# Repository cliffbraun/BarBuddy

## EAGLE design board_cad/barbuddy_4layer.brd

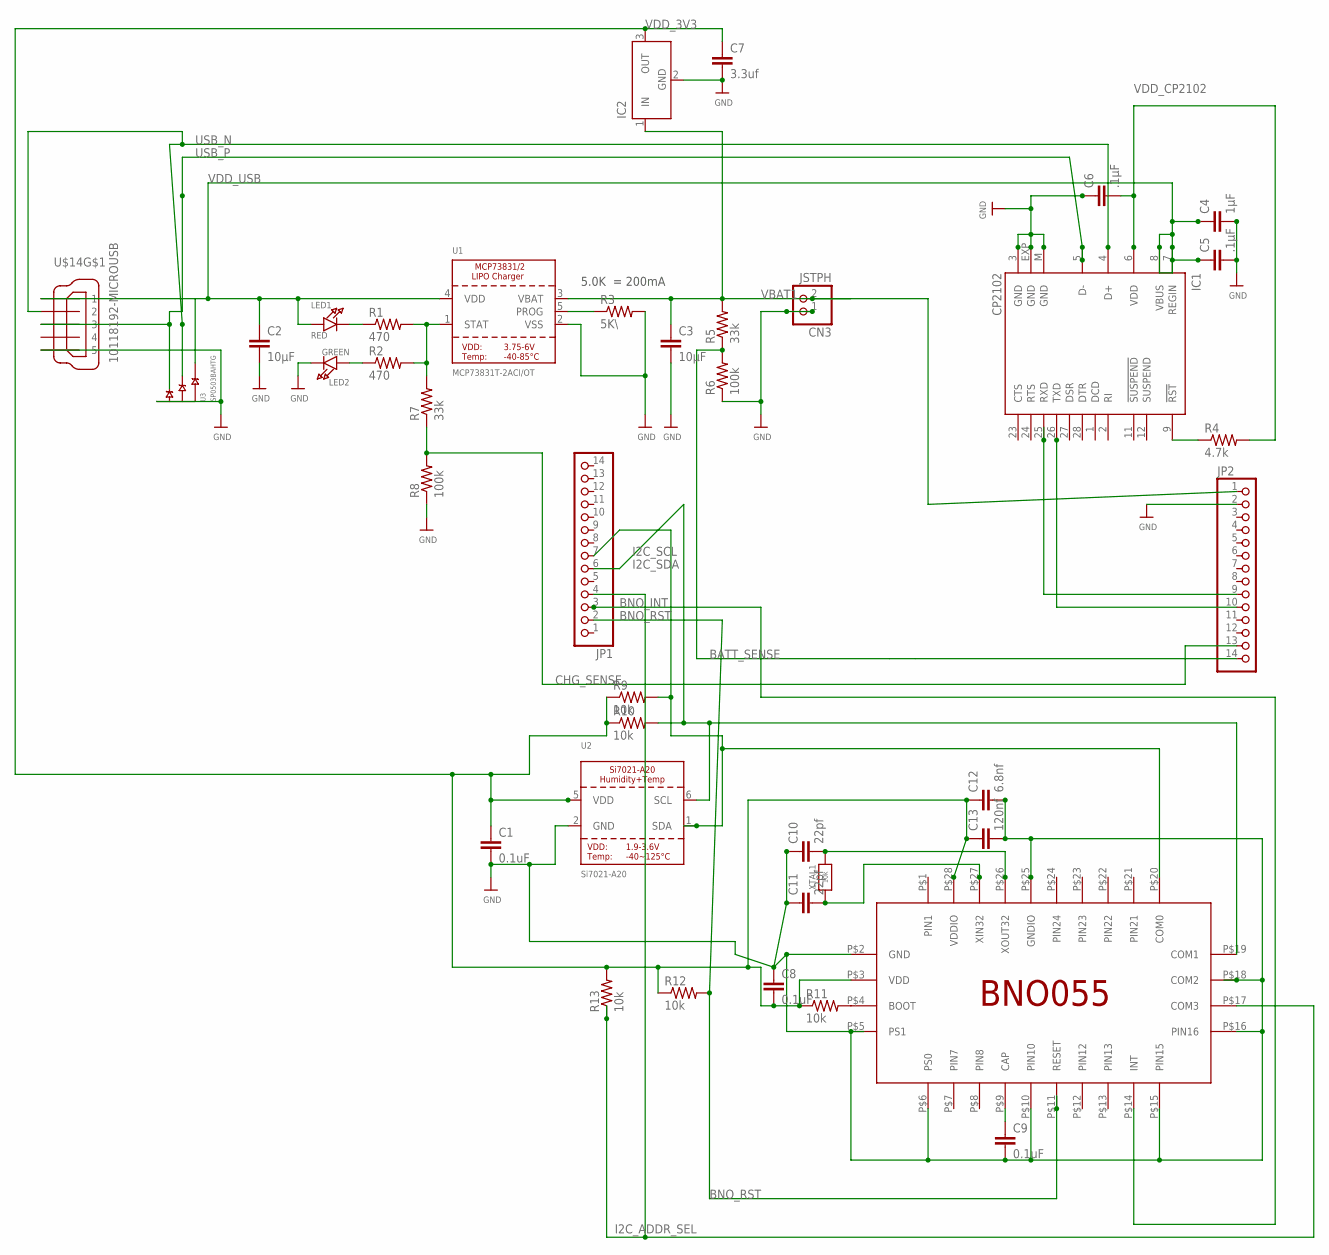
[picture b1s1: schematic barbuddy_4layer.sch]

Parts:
BNO055: BNO055; LGA-28
C1, C8, C9: 0.1uF; C0402
C2, C3: 10µF; C0402
C4: 1µF; C0402
C5, C6: .1µF; C0402
C7: 3.3uf; C0402
C10, C11: 22pf; C0402
C12: 6.8nf; C0402
C13: 120nf; C0402
CN3: JSTPH; JSTPH2
IC1: CP2102; MLP28
IC2: LT1129CST5; SOT223
JP1, JP2: PINHD-1X14; 1X14
LED1: RED; CHIPLED_0805_NOOUTLINE
LED2: GREEN; CHIPLED_0805_NOOUTLINE
R1, R2: 470; R0402
R3: 5K\; R0402
R4: 4.7k; R0402
R5, R7: 33k; R0402
R6, R8: 100k; R0402
R9, R10, R11, R12, R13: 10k; R0402
U1: MCP73831T-2ACI/OT; SOT23-5
U2: Si7021-A20; DFN6_3X3_SI
U3: SP0503BAHTG; SOT143
U$14: 10118192-MICROUSB; MICROUSB-SMT
XTAL1: 10k; 0805-NO

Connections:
BATT_SENSE: JP2.14, R5.1, R6.2
BNO_CAP: BNO055.P$9 (CAP), C9.1
BNO_INT: BNO055.P$14 (INT), JP1.3
BNO_RST: BNO055.P$11 (RESET), JP1.2, R12.2
CHG_PROG: R3.1, U1.5 (PROG)
CHG_SENSE: JP2.13, R7.1, R8.2
CHG_STATUS: R1.2, R2.2, R7.2, U1.1 (STAT)
CP2102_RST: IC1.9 (!RST), R4.1
GND: BNO055.P$2 (GND), BNO055.P$5 (PS1), BNO055.P$6 (PS0), BNO055.P$10 (PIN10), BNO055.P$15 (PIN15), BNO055.P$16 (PIN16), BNO055.P$18 (COM2), BNO055.P$25 (GNDIO), C1.2, C2.2, C3.2, C4.2, C5.2, C6.1, C7.2, C8.1, C9.2, C10.1, C11.1, C12.2, C13.2, CN3.1, IC1.3 (GND), IC1.EXP (GND), IC1.M (GND), IC2.2 (GND), IC2.4 (GND), JP2.2, LED2.C, R3.2, R6.1, R8.1, U1.2 (VSS), U2.2 (GND), U3.1 (GND), U$14.P$5 (5)
I2C_ADDR_SEL: BNO055.P$17 (COM3), JP1.4, R13.1
I2C_SCL: BNO055.P$19 (COM1), JP1.6, R10.2, U2.6 (SCL)
I2C_SDA: BNO055.P$20 (COM0), JP1.7, R9.2, U2.1 (SDA)
unnamed: LED1.C, R1.1
unnamed: BNO055.P$4 (BOOT), R11.2
unnamed: LED2.A, R2.1
UART0_RX: IC1.26 (TXD), JP2.10
UART0_TX: IC1.25 (RXD), JP2.9
USB_N: IC1.4 (D+), U3.3 (B), U$14.P$2 (2)
USB_P: IC1.5 (D-), U3.2 (A), U$14.P$3 (3)
VBAT1: C3.1, CN3.2, IC2.1 (IN), JP2.1, R5.2, U1.3 (VBAT)
VDD_3V3: BNO055.P$3 (VDD), BNO055.P$28 (VDDIO), C1.1, C7.1, C8.2, C12.1, C13.1, IC2.3 (OUT), R9.1, R10.1, R11.1, R12.1, R13.2, U2.5 (VDD)
VDD_CP2102: C6.2, IC1.6 (VDD), R4.2
VDD_USB: C2.1, C4.1, C5.1, IC1.7 (REGIN), IC1.8 (VBUS), LED1.A, U1.4 (VDD), U3.4 (C), U$14.P$1 (1)
X_IN: BNO055.P$27 (XIN32), C11.2, XTAL1.1
X_OUT: BNO055.P$26 (XOUT32), C10.2, XTAL1.2

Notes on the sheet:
5.0K = 200mA

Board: 4 copper layers, 39 parts (16 on the bottom side), 25 nets, no tracks yet.

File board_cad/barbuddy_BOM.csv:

"Part";"Value";"Device";"Package";"Description";"MF";"MPN";"OC_FARNELL";"OC_NEWARK";
"BNO055";"BNO055";"BNO055";"LGA-28";"";"";"";"";"";
"C1";"0.1uF";"C-EUC0402";"C0402";"CAPACITOR, European symbol";"";"";"";"";
"C2";"10µF";"C-EUC0402";"C0402";"CAPACITOR, European symbol";"";"";"";"";
"C3";"10µF";"C-EUC0402";"C0402";"CAPACITOR, European symbol";"";"";"";"";
"C4";"1µF";"C-EUC0402";"C0402";"CAPACITOR, European symbol";"";"";"";"";
"C5";".1µF";"C-EUC0402";"C0402";"CAPACITOR, European symbol";"";"";"";"";
"C6";".1µF";"C-EUC0402";"C0402";"CAPACITOR, European symbol";"";"";"";"";
"C7";"3.3uf";"C-EUC0402";"C0402";"CAPACITOR, European symbol";"";"";"";"";
"C8";"0.1uF";"C-EUC0402";"C0402";"CAPACITOR, European symbol";"";"";"";"";
"C9";"0.1uF";"C-EUC0402";"C0402";"CAPACITOR, European symbol";"";"";"";"";
"C10";"22pf";"C-EUC0402";"C0402";"CAPACITOR, European symbol";"";"";"";"";
"C11";"22pf";"C-EUC0402";"C0402";"CAPACITOR, European symbol";"";"";"";"";
"C12";"6.8nf";"C-EUC0402";"C0402";"CAPACITOR, European symbol";"";"";"";"";
"C13";"120nf";"C-EUC0402";"C0402";"CAPACITOR, European symbol";"";"";"";"";
"CN3";"JSTPH";"JST_2PIN";"JSTPH2";"JST 2-Pin Right-Angle Connector";"";"";"";"";
"IC1";"CP2102";"CP2102";"MLP28";"Single-Chip USB to UART Bridge";"FARNELL";"CP2102-GM";"9282130";"30K5635";
"IC2";"";"LT1129CST5";"SOT223";"VOLTAGE REGULATOR";"";"";"";"";
"JP1";"";"PINHD-1X14";"1X14";"PIN HEADER";"";"";"";"";
"JP2";"";"PINHD-1X14";"1X14";"PIN HEADER";"";"";"";"";
"LED1";"RED";"LED0805_NOOUTLINE";"CHIPLED_0805_NOOUTLINE";"LED";"";"";"";"";
"LED2";"GREEN";"LED0805_NOOUTLINE";"CHIPLED_0805_NOOUTLINE";"LED";"";"";"";"";
"R1";"470";"R-US_R0402";"R0402";"RESISTOR, American symbol";"";"";"";"";
"R2";"470";"R-US_R0402";"R0402";"RESISTOR, American symbol";"";"";"";"";
"R3";"5K\";"R-US_R0402";"R0402";"RESISTOR, American symbol";"";"";"";"";
"R4";"4.7k";"R-US_R0402";"R0402";"RESISTOR, American symbol";"";"";"";"";
"R5";"33k";"R-US_R0402";"R0402";"RESISTOR, American symbol";"";"";"";"";
"R6";"100k";"R-US_R0402";"R0402";"RESISTOR, American symbol";"";"";"";"";
"R7";"33k";"R-US_R0402";"R0402";"RESISTOR, American symbol";"";"";"";"";
"R8";"100k";"R-US_R0402";"R0402";"RESISTOR, American symbol";"";"";"";"";
"R9";"10k";"R-US_R0402";"R0402";"RESISTOR, American symbol";"";"";"";"";
"R10";"10k";"R-US_R0402";"R0402";"RESISTOR, American symbol";"";"";"";"";
"R11";"10k";"R-US_R0402";"R0402";"RESISTOR, American symbol";"";"";"";"";
"R12";"10k";"R-US_R0402";"R0402";"RESISTOR, American symbol";"";"";"";"";
"R13";"10k";"R-US_R0402";"R0402";"RESISTOR, American symbol";"";"";"";"";
"U$13";"";"USB-AB""";"USB-AB-MICRO-SMD_V02_BOSS";"This is a USB AB connector that is compatible with USB OTG. i.e. this connector can serve as a host or device";"";"";"";"";
"U1";"MCP73831T-2ACI/OT";"MCP73831/2";"SOT23-5";"MCP73831/2 LIPO Charger";"";"";"";"";
"U2";"Si7021-A20";"SI7021-A20";"DFN6_3X3_SI";"Si7021-A20 - I2C Humidity and Temperature Sensor";"";"";"";"";
"U3";"SP0503BAHTG";"SP0503BAHTG";"SOT143";"";"";"";"";"";
"XTAL1";"10k";"RESISTOR0805_NOOUTLINE";"0805-NO";"Resistors";"";"";"";"";

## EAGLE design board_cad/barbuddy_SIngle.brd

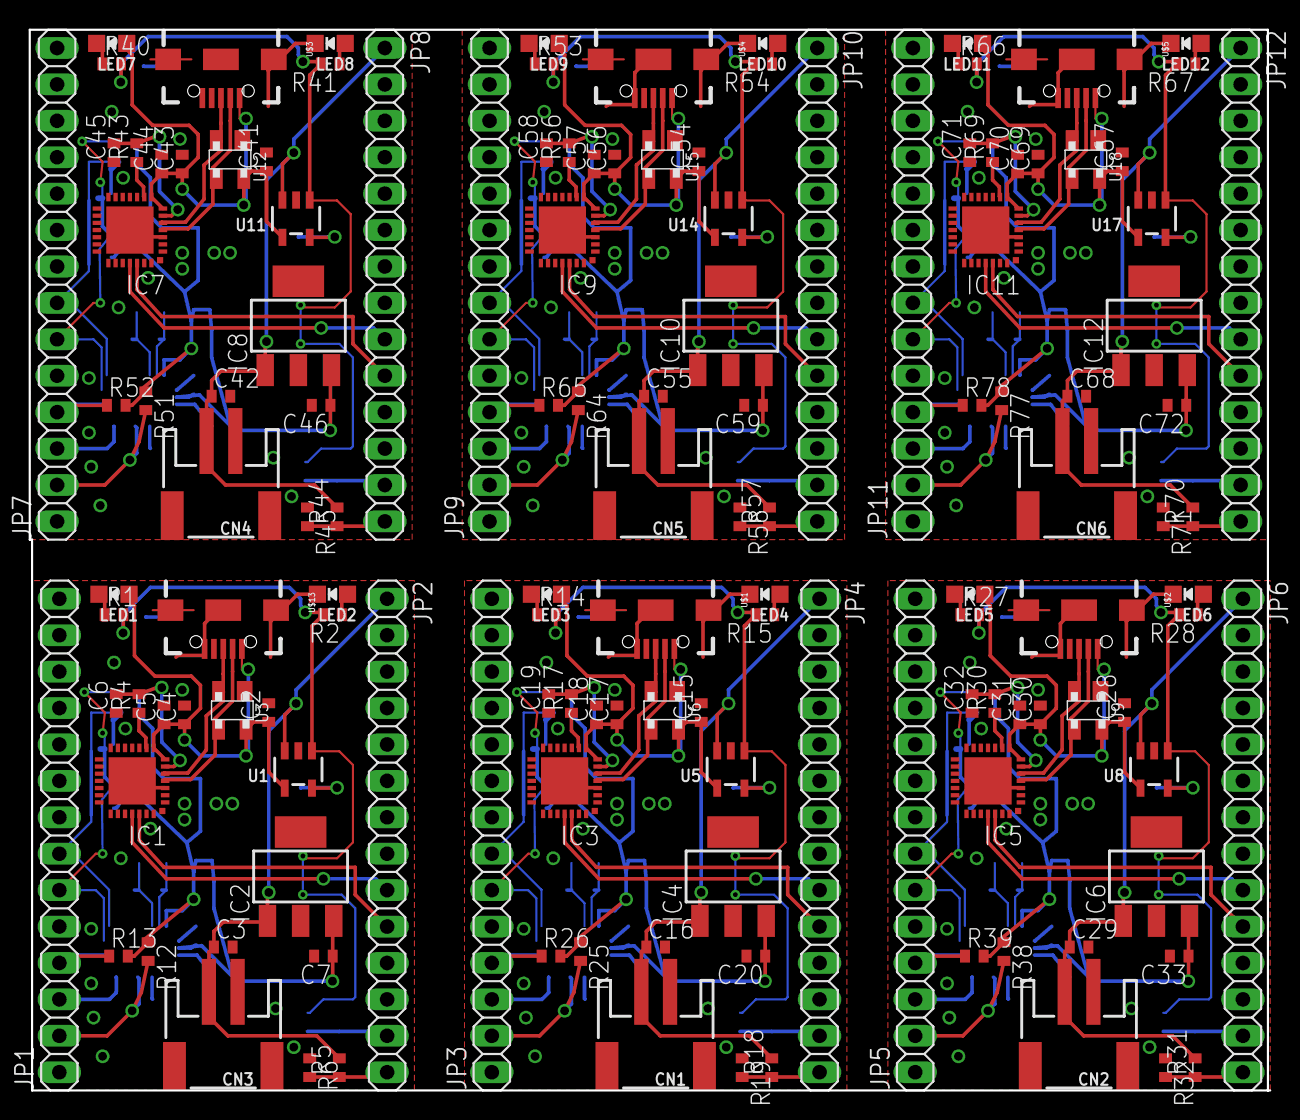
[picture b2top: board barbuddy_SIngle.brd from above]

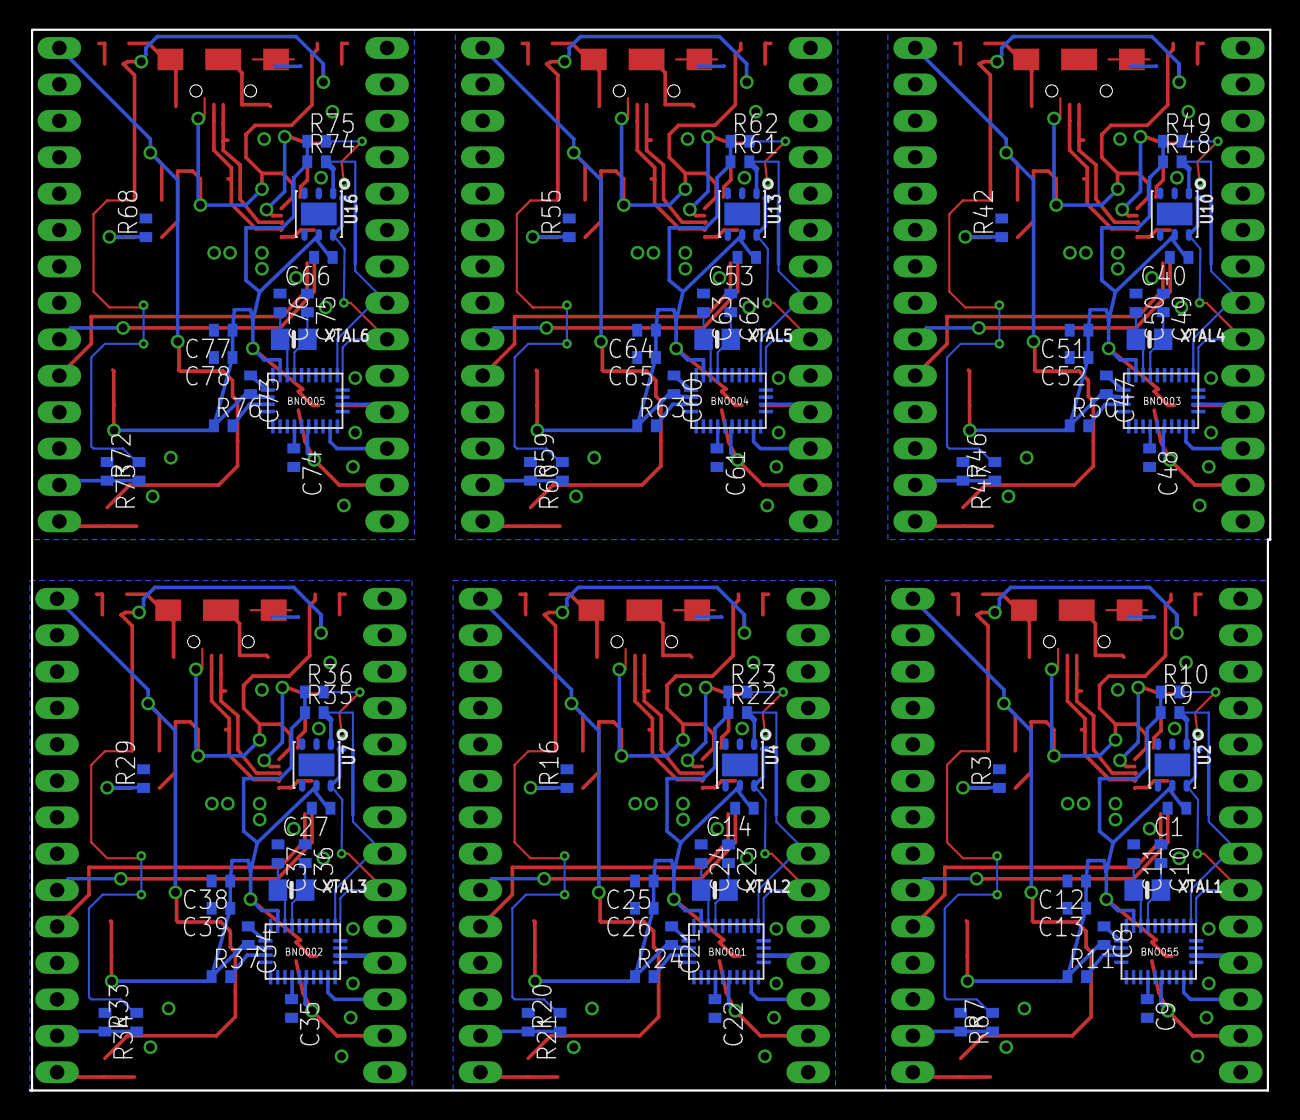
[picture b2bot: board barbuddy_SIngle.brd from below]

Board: 2 copper layers, 86.5 x 74.0 mm, 234 parts (96 on the bottom side), 150 nets.

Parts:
BNO001, BNO002, BNO003, BNO004, BNO005, BNO055: BNO055; LGA-28
C1, C8, C9, C14, C21, C22, C27, C34, C35, C40, C47, C48, C53, C60, C61, C66, C73, C74: 0.1uF; C0402
C2, C3, C15, C16, C28, C29, C41, C42, C54, C55, C67, C68: 10µF; C0402
C4, C17, C30, C43, C56, C69: 1µF; C0402
C5, C6, C18, C19, C31, C32, C44, C45, C57, C58, C70, C71: .1µF; C0402
C7, C20, C33, C46, C59, C72: 3.3uf; C0402
C10, C11, C23, C24, C36, C37, C49, C50, C62, C63, C75, C76: 22pf; C0402
C12, C25, C38, C51, C64, C77: 6.8nf; C0402
C13, C26, C39, C52, C65, C78: 120nf; C0402
CN1, CN2, CN3, CN4, CN5, CN6: JSTPH; JSTPH2
IC1, IC3, IC5, IC7, IC9, IC11: CP2102; MLP28
IC2, IC4, IC6, IC8, IC10, IC12: SOT223
JP1, JP2, JP3, JP4, JP5, JP6, JP7, JP8, JP9, JP10, JP11, JP12: 1X14
LED1, LED3, LED5, LED7, LED9, LED11: RED; CHIPLED_0805_NOOUTLINE
LED2, LED4, LED6, LED8, LED10, LED12: GREEN; CHIPLED_0805_NOOUTLINE
R1, R2, R14, R15, R27, R28, R40, R41, R53, R54, R66, R67: 470; R0402
R3, R16, R29, R42, R55, R68: 5K\; R0402
R4, R17, R30, R43, R56, R69: 4.7k; R0402
R5, R7, R18, R20, R31, R33, R44, R46, R57, R59, R70, R72: 33k; R0402
R6, R8, R19, R21, R32, R34, R45, R47, R58, R60, R71, R73: 100k; R0402
R9, R10, R11, R12, R13, R22, R23, R24, R25, R26, R35, R36, R37, R38, R39, R48, R49, R50, R51, R52, R61, R62, R63, R64, R65, R74, R75, R76, R77, R78: 10k; R0402
U1, U5, U8, U11, U14, U17: MCP73831T-2ACI/OT; SOT23-5
U2, U4, U7, U10, U13, U16: Si7021-A20; DFN6_3X3_SI
U3, U6, U9, U12, U15, U18: SP0503BAHTG; SOT143
U$1, U$2, U$3, U$4, U$5, U$13: USB-AB-MICRO-SMD_V02_BOSS
XTAL1, XTAL2, XTAL3, XTAL4, XTAL5, XTAL6: 10k; 0805-NO

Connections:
BATT_SENSE: JP2.14, R5.1, R6.2
BATT_SENSE1: JP4.14, R18.1, R19.2
BATT_SENSE2: JP6.14, R31.1, R32.2
BATT_SENSE3: JP8.14, R44.1, R45.2
BATT_SENSE4: JP10.14, R57.1, R58.2
BATT_SENSE5: JP12.14, R70.1, R71.2
BNO_CAP: BNO055.P$9, C9.1
BNO_CAP1: BNO001.P$9, C22.1
BNO_CAP2: BNO002.P$9, C35.1
BNO_CAP3: BNO003.P$9, C48.1
BNO_CAP4: BNO004.P$9, C61.1
BNO_CAP5: BNO005.P$9, C74.1
BNO_INT: BNO055.P$14, JP1.3
BNO_INT1: BNO001.P$14, JP3.3
BNO_INT2: BNO002.P$14, JP5.3
BNO_INT3: BNO003.P$14, JP7.3
BNO_INT4: BNO004.P$14, JP9.3
BNO_INT5: BNO005.P$14, JP11.3
BNO_RST: BNO055.P$11, JP1.2, R12.2
BNO_RST1: BNO001.P$11, JP3.2, R25.2
BNO_RST2: BNO002.P$11, JP5.2, R38.2
BNO_RST3: BNO003.P$11, JP7.2, R51.2
BNO_RST4: BNO004.P$11, JP9.2, R64.2
BNO_RST5: BNO005.P$11, JP11.2, R77.2
CHG_PROG: R3.1, U1.5
CHG_PROG1: R16.1, U5.5
CHG_PROG2: R29.1, U8.5
CHG_PROG3: R42.1, U11.5
CHG_PROG4: R55.1, U14.5
CHG_PROG5: R68.1, U17.5
CHG_SENSE: JP2.13, R7.1, R8.2
CHG_SENSE1: JP4.13, R20.1, R21.2
CHG_SENSE2: JP6.13, R33.1, R34.2
CHG_SENSE3: JP8.13, R46.1, R47.2
CHG_SENSE4: JP10.13, R59.1, R60.2
CHG_SENSE5: JP12.13, R72.1, R73.2
CHG_STATUS: R1.2, R2.2, R7.2, U1.1
CHG_STATUS1: R14.2, R15.2, R20.2, U5.1
CHG_STATUS2: R27.2, R28.2, R33.2, U8.1
CHG_STATUS3: R40.2, R41.2, R46.2, U11.1
CHG_STATUS4: R53.2, R54.2, R59.2, U14.1
CHG_STATUS5: R66.2, R67.2, R72.2, U17.1
CP2102_RST: IC1.9, R4.1
CP2102_RST1: IC3.9, R17.1
CP2102_RST2: IC5.9, R30.1
CP2102_RST3: IC7.9, R43.1
CP2102_RST4: IC9.9, R56.1
CP2102_RST5: IC11.9, R69.1
GND: BNO055.P$2, BNO055.P$5, BNO055.P$6, BNO055.P$10, BNO055.P$15, BNO055.P$16, BNO055.P$18, BNO055.P$25, C1.2, C2.2, C3.2, C4.2, C5.2, C6.1, C7.2, C8.1, C9.2, C10.1, C11.1, C12.2, C13.2, CN3.1, IC1.3, IC1.EXP, IC1.M, IC2.2, IC2.4, JP2.2, LED2.C, R3.2, R6.1, R8.1, U1.2, U2.2, U3.1
GND2: BNO001.P$2, BNO001.P$5, BNO001.P$6, BNO001.P$10, BNO001.P$15, BNO001.P$16, BNO001.P$18, BNO001.P$25, C14.2, C15.2, C16.2, C17.2, C18.2, C19.1, C20.2, C21.1, C22.2, C23.1, C24.1, C25.2, C26.2, CN1.1, IC3.3, IC3.EXP, IC3.M, IC4.2, IC4.4, JP4.2, LED4.C, R16.2, R19.1, R21.1, U4.2, U5.2, U6.1
GND4: BNO002.P$2, BNO002.P$5, BNO002.P$6, BNO002.P$10, BNO002.P$15, BNO002.P$16, BNO002.P$18, BNO002.P$25, C27.2, C28.2, C29.2, C30.2, C31.2, C32.1, C33.2, C34.1, C35.2, C36.1, C37.1, C38.2, C39.2, CN2.1, IC5.3, IC5.EXP, IC5.M, IC6.2, IC6.4, JP6.2, LED6.C, R29.2, R32.1, R34.1, U7.2, U8.2, U9.1
GND6: BNO003.P$2, BNO003.P$5, BNO003.P$6, BNO003.P$10, BNO003.P$15, BNO003.P$16, BNO003.P$18, BNO003.P$25, C40.2, C41.2, C42.2, C43.2, C44.2, C45.1, C46.2, C47.1, C48.2, C49.1, C50.1, C51.2, C52.2, CN4.1, IC7.3, IC7.EXP, IC7.M, IC8.2, IC8.4, JP8.2, LED8.C, R42.2, R45.1, R47.1, U10.2, U11.2, U12.1
GND8: BNO004.P$2, BNO004.P$5, BNO004.P$6, BNO004.P$10, BNO004.P$15, BNO004.P$16, BNO004.P$18, BNO004.P$25, C53.2, C54.2, C55.2, C56.2, C57.2, C58.1, C59.2, C60.1, C61.2, C62.1, C63.1, C64.2, C65.2, CN5.1, IC9.3, IC9.EXP, IC9.M, IC10.2, IC10.4, JP10.2, LED10.C, R55.2, R58.1, R60.1, U13.2, U14.2, U15.1
GND10: BNO005.P$2, BNO005.P$5, BNO005.P$6, BNO005.P$10, BNO005.P$15, BNO005.P$16, BNO005.P$18, BNO005.P$25, C66.2, C67.2, C68.2, C69.2, C70.2, C71.1, C72.2, C73.1, C74.2, C75.1, C76.1, C77.2, C78.2, CN6.1, IC11.3, IC11.EXP, IC11.M, IC12.2, IC12.4, JP12.2, LED12.C, R68.2, R71.1, R73.1, U16.2, U17.2, U18.1
I2C_ADDR_SEL: BNO055.P$17, JP1.4, R13.1
I2C_ADDR_SEL1: BNO001.P$17, JP3.4, R26.1
I2C_ADDR_SEL2: BNO002.P$17, JP5.4, R39.1
I2C_ADDR_SEL3: BNO003.P$17, JP7.4, R52.1
I2C_ADDR_SEL4: BNO004.P$17, JP9.4, R65.1
I2C_ADDR_SEL5: BNO005.P$17, JP11.4, R78.1
I2C_SCL: BNO055.P$19, JP1.6, R10.2, U2.6
I2C_SCL1: BNO001.P$19, JP3.6, R23.2, U4.6
I2C_SCL2: BNO002.P$19, JP5.6, R36.2, U7.6
I2C_SCL3: BNO003.P$19, JP7.6, R49.2, U10.6
I2C_SCL4: BNO004.P$19, JP9.6, R62.2, U13.6
I2C_SCL5: BNO005.P$19, JP11.6, R75.2, U16.6
I2C_SDA: BNO055.P$20, JP1.7, R9.2, U2.1
I2C_SDA1: BNO001.P$20, JP3.7, R22.2, U4.1
I2C_SDA2: BNO002.P$20, JP5.7, R35.2, U7.1
I2C_SDA3: BNO003.P$20, JP7.7, R48.2, U10.1
I2C_SDA4: BNO004.P$20, JP9.7, R61.2, U13.1
I2C_SDA5: BNO005.P$20, JP11.7, R74.2, U16.1
unnamed: LED1.C, R1.1
unnamed: LED3.C, R14.1
unnamed: BNO055.P$4, R11.2
unnamed: LED4.A, R15.1
unnamed: BNO001.P$4, R24.2
unnamed: LED2.A, R2.1
unnamed: LED5.C, R27.1
unnamed: LED6.A, R28.1
unnamed: BNO002.P$4, R37.2
unnamed: LED7.C, R40.1
unnamed: LED8.A, R41.1
unnamed: BNO003.P$4, R50.2
unnamed: LED9.C, R53.1
unnamed: LED10.A, R54.1
unnamed: BNO004.P$4, R63.2
unnamed: LED11.C, R66.1
unnamed: LED12.A, R67.1
unnamed: BNO005.P$4, R76.2
UART0_RX: IC1.26, JP2.10
UART0_RX1: IC3.26, JP4.10
UART0_RX2: IC5.26, JP6.10
UART0_RX3: IC7.26, JP8.10
UART0_RX4: IC9.26, JP10.10
UART0_RX5: IC11.26, JP12.10
UART0_TX: IC1.25, JP2.9
UART0_TX1: IC3.25, JP4.9
UART0_TX2: IC5.25, JP6.9
UART0_TX3: IC7.25, JP8.9
UART0_TX4: IC9.25, JP10.9
UART0_TX5: IC11.25, JP12.9
USB_N: IC1.4, U3.3
USB_N1: IC3.4, U6.3
USB_N2: IC5.4, U9.3
USB_N3: IC7.4, U12.3
USB_N4: IC9.4, U15.3
USB_N5: IC11.4, U18.3
USB_P: IC1.5, U3.2
USB_P1: IC3.5, U6.2
USB_P2: IC5.5, U9.2
USB_P3: IC7.5, U12.2
USB_P4: IC9.5, U15.2
USB_P5: IC11.5, U18.2
VBAT1: C3.1, CN3.2, IC2.1, JP2.1, R5.2, U1.3
VBAT2: C16.1, CN1.2, IC4.1, JP4.1, R18.2, U5.3
VBAT3: C29.1, CN2.2, IC6.1, JP6.1, R31.2, U8.3
VBAT4: C42.1, CN4.2, IC8.1, JP8.1, R44.2, U11.3
VBAT5: C55.1, CN5.2, IC10.1, JP10.1, R57.2, U14.3
VBAT6: C68.1, CN6.2, IC12.1, JP12.1, R70.2, U17.3
VDD_3V1: BNO001.P$3, BNO001.P$28, C14.1, C20.1, C21.2, C25.1, C26.1, IC4.3, R22.1, R23.1, R24.1, R25.1, R26.2, U4.5
VDD_3V2: BNO002.P$3, BNO002.P$28, C27.1, C33.1, C34.2, C38.1, C39.1, IC6.3, R35.1, R36.1, R37.1, R38.1, R39.2, U7.5
VDD_3V3: BNO055.P$3, BNO055.P$28, C1.1, C7.1, C8.2, C12.1, C13.1, IC2.3, R9.1, R10.1, R11.1, R12.1, R13.2, U2.5
VDD_3V4: BNO003.P$3, BNO003.P$28, C40.1, C46.1, C47.2, C51.1, C52.1, IC8.3, R48.1, R49.1, R50.1, R51.1, R52.2, U10.5
VDD_3V5: BNO004.P$3, BNO004.P$28, C53.1, C59.1, C60.2, C64.1, C65.1, IC10.3, R61.1, R62.1, R63.1, R64.1, R65.2, U13.5
VDD_3V6: BNO005.P$3, BNO005.P$28, C66.1, C72.1, C73.2, C77.1, C78.1, IC12.3, R74.1, R75.1, R76.1, R77.1, R78.2, U16.5
VDD_CP1: C19.2, IC3.6, R17.2
VDD_CP2: C32.2, IC5.6, R30.2
VDD_CP3: C45.2, IC7.6, R43.2
VDD_CP4: C58.2, IC9.6, R56.2
VDD_CP5: C71.2, IC11.6, R69.2
VDD_CP2102: C6.2, IC1.6, R4.2
VDD_USB: C2.1, C4.1, C5.1, IC1.7, IC1.8, LED1.A, U1.4, U3.4, U$13.VBUS1
VDD_USB1: C15.1, C17.1, C18.1, IC3.7, IC3.8, LED3.A, U5.4, U6.4, U$1.VBUS1
VDD_USB2: C28.1, C30.1, C31.1, IC5.7, IC5.8, LED5.A, U8.4, U9.4, U$2.VBUS1
VDD_USB3: C41.1, C43.1, C44.1, IC7.7, IC7.8, LED7.A, U11.4, U12.4, U$3.VBUS1
VDD_USB4: C54.1, C56.1, C57.1, IC9.7, IC9.8, LED9.A, U14.4, U15.4, U$4.VBUS1
VDD_USB5: C67.1, C69.1, C70.1, IC11.7, IC11.8, LED11.A, U17.4, U18.4, U$5.VBUS1
X_IN: BNO055.P$27, C11.2, XTAL1.1
X_IN1: BNO001.P$27, C24.2, XTAL2.1
X_IN2: BNO002.P$27, C37.2, XTAL3.1
X_IN3: BNO003.P$27, C50.2, XTAL4.1
X_IN4: BNO004.P$27, C63.2, XTAL5.1
X_IN5: BNO005.P$27, C76.2, XTAL6.1
X_OUT: BNO055.P$26, C10.2, XTAL1.2
X_OUT1: BNO001.P$26, C23.2, XTAL2.2
X_OUT2: BNO002.P$26, C36.2, XTAL3.2
X_OUT3: BNO003.P$26, C49.2, XTAL4.2
X_OUT4: BNO004.P$26, C62.2, XTAL5.2
X_OUT5: BNO005.P$26, C75.2, XTAL6.2

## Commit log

2016-11-29 Board cad as manufactured
2016-12-14 Report
2016-12-19 minor report changes

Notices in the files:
parts and their libraries:
microbuilder: This work is placed in the public domain, and may be freely used for commercial and non-commercial work with the following conditions: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
